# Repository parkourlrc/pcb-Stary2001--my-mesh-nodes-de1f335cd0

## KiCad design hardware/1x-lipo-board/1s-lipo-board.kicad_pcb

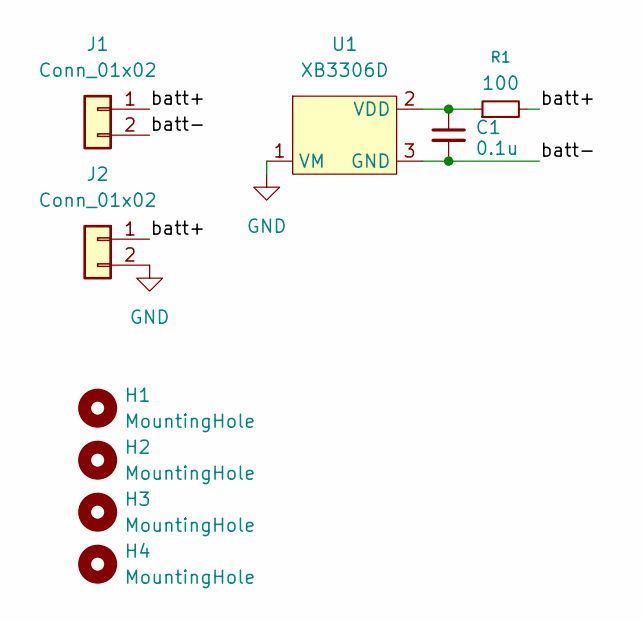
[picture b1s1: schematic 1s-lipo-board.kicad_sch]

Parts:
C1: 0.1u; C_0603_1608Metric
H1, H2, H3, H4: MountingHole; MountingHole_3.2mm_M3
J1: Conn_01x02; BatteryHolder_MPD_BK-18650-PC2
J2: Conn_01x02; JST_PH_S2B-PH-K_1x02_P2.00mm_Horizontal
R1: 100; R_0603_1608Metric
U1: XB3306D; SOT-23-3

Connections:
/batt+: J1.1, J2.1, R1.2
/batt-: C1.2, J1.2, U1.3 (GND)
GND: J2.2, U1.1 (VM)
unnamed: C1.1, R1.1, U1.2 (VDD)

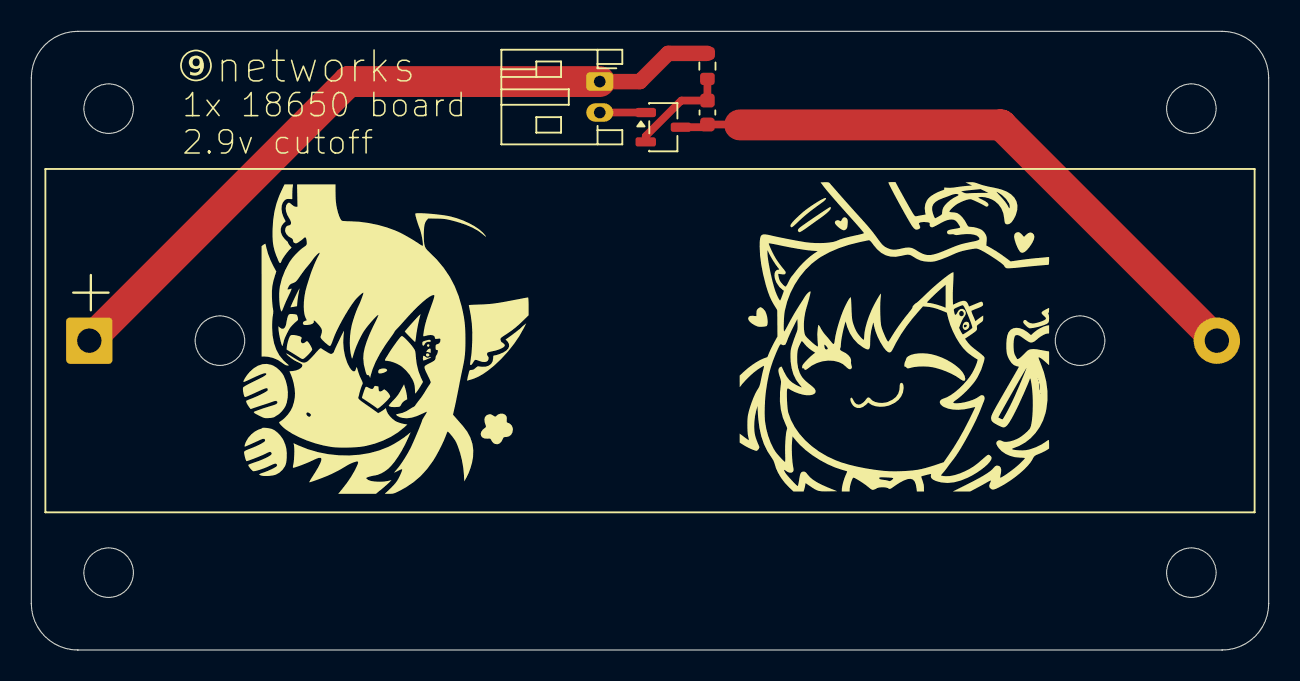
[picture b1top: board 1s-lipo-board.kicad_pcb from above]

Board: 2 copper layers, 80.0 x 40.0 mm, 9 parts (0 on the bottom side), 4 nets.

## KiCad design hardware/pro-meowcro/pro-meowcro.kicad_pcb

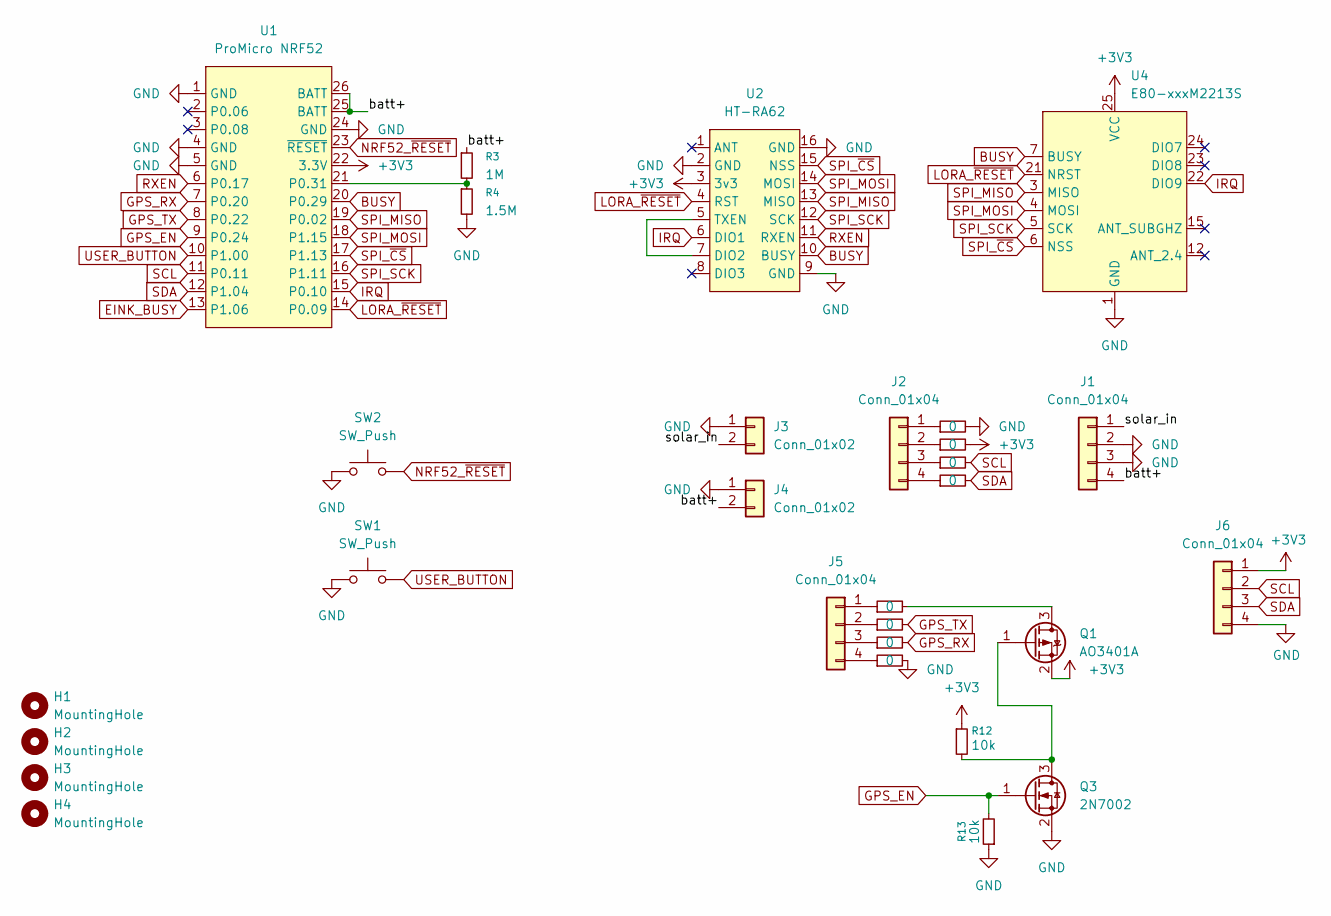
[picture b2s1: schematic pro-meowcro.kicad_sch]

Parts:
H1, H2, H3, H4: MountingHole; MountingHole_3.2mm_M3
J1, J2, J5: Conn_01x04; PinHeader_1x04_P2.54mm_Vertical
J3: Conn_01x02; JST_XH_B2B-XH-A_1x02_P2.50mm_Vertical
J4: Conn_01x02; JST_PH_B2B-PH-K_1x02_P2.00mm_Vertical
J6: Conn_01x04; JST_XH_B4B-XH-A_1x04_P2.50mm_Vertical
Q1: AO3401A; SOT-23
Q3: 2N7002; SOT-23
R1, R2, R5, R6, R7, R8, R9, R10: 0; R_0603_1608Metric
R3: 1M; R_0603_1608Metric
R4: 1.5M; R_0603_1608Metric
R12, R13: 10k; R_0603_1608Metric
SW1, SW2: SW_Push; SW_Tactile_SPST_NO_Straight_CK_PTS636Sx25SMTRLFS
U1: ProMicro NRF52; ProMicro_NRF52
U2: HT-RA62
U4: E80-xxxM2213S

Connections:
+3V3: J6.1, Q1.2 (S), R2.2, R12.1, U1.22 (3.3V), U2.3 (3v3), U4.25 (VCC)
/batt+: J1.4, J4.2, R3.1, U1.25 (BATT), U1.26 (BATT)
/solar_in: J1.1, J3.2
BUSY: U1.20 (P0.29), U2.10 (BUSY), U4.7 (BUSY)
EINK_BUSY: U1.13 (P1.06)
GND: J1.2, J1.3, J3.1, J4.1, J6.4, Q3.2 (S), R1.2, R4.2, R10.2, R13.1, SW1.1, SW2.1, U1.1 (GND), U1.4 (GND), U1.5 (GND), U1.24 (GND), U2.2 (GND), U2.9 (GND), U2.16 (GND), U4.1 (GND), U4.8 (GND), U4.11 (GND), U4.13 (GND), U4.14 (GND), U4.16 (GND), U4.19 (GND), U4.26 (GND)
GPS_EN: Q3.1 (G), R13.2, U1.9 (P0.24)
GPS_RX: R9.2, U1.7 (P0.20)
GPS_TX: R8.2, U1.8 (P0.22)
IRQ: U1.15 (P0.10), U2.6 (DIO1), U4.22 (DIO9)
LORA_~RESET: U1.14 (P0.09), U2.4 (RST), U4.21 (NRST)
NRF52_~RESET: SW2.2, U1.23 (~RESET)
unnamed: J2.1, R1.1
unnamed: J2.2, R2.1
unnamed: J2.3, R5.1
unnamed: J2.4, R6.1
unnamed: J5.1, R7.1
unnamed: J5.2, R8.1
unnamed: J5.3, R9.1
unnamed: J5.4, R10.1
unnamed: Q1.3 (D), R7.2
unnamed: Q1.1 (G), Q3.3 (D), R12.2
unnamed: R3.2, R4.1, U1.21 (P0.31)
unnamed: U2.5 (TXEN), U2.7 (DIO2)
RXEN: U1.6 (P0.17), U2.11 (RXEN)
SCL: J6.2, R5.2, U1.11 (P0.11)
SDA: J6.3, R6.2, U1.12 (P1.04)
SPI_MISO: U1.19 (P0.02), U2.13 (MISO), U4.3 (MISO)
SPI_MOSI: U1.18 (P1.15), U2.14 (MOSI), U4.4 (MOSI)
SPI_SCK: U1.16 (P1.11), U2.12 (SCK), U4.5 (SCK)
SPI_~CS: U1.17 (P1.13), U2.15 (NSS), U4.6 (NSS)
USER_BUTTON: SW1.2, U1.10 (P1.00)

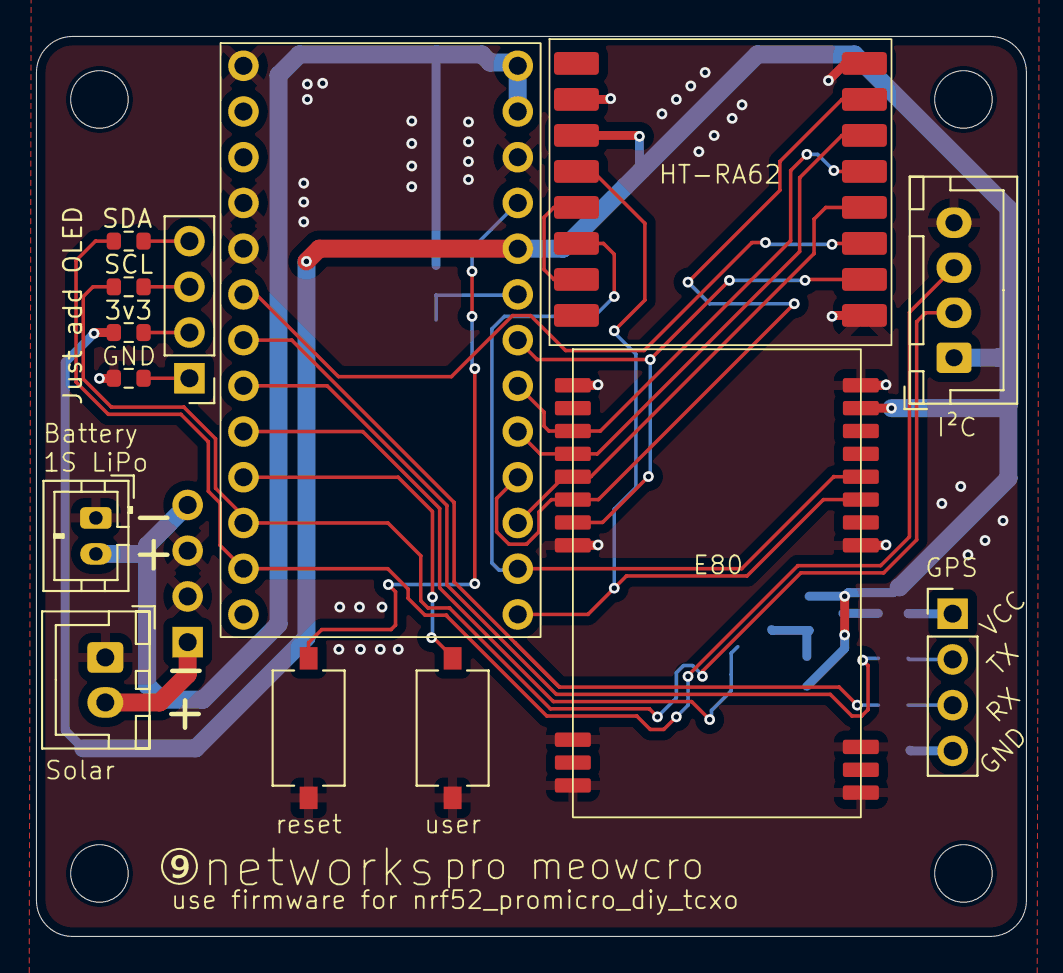
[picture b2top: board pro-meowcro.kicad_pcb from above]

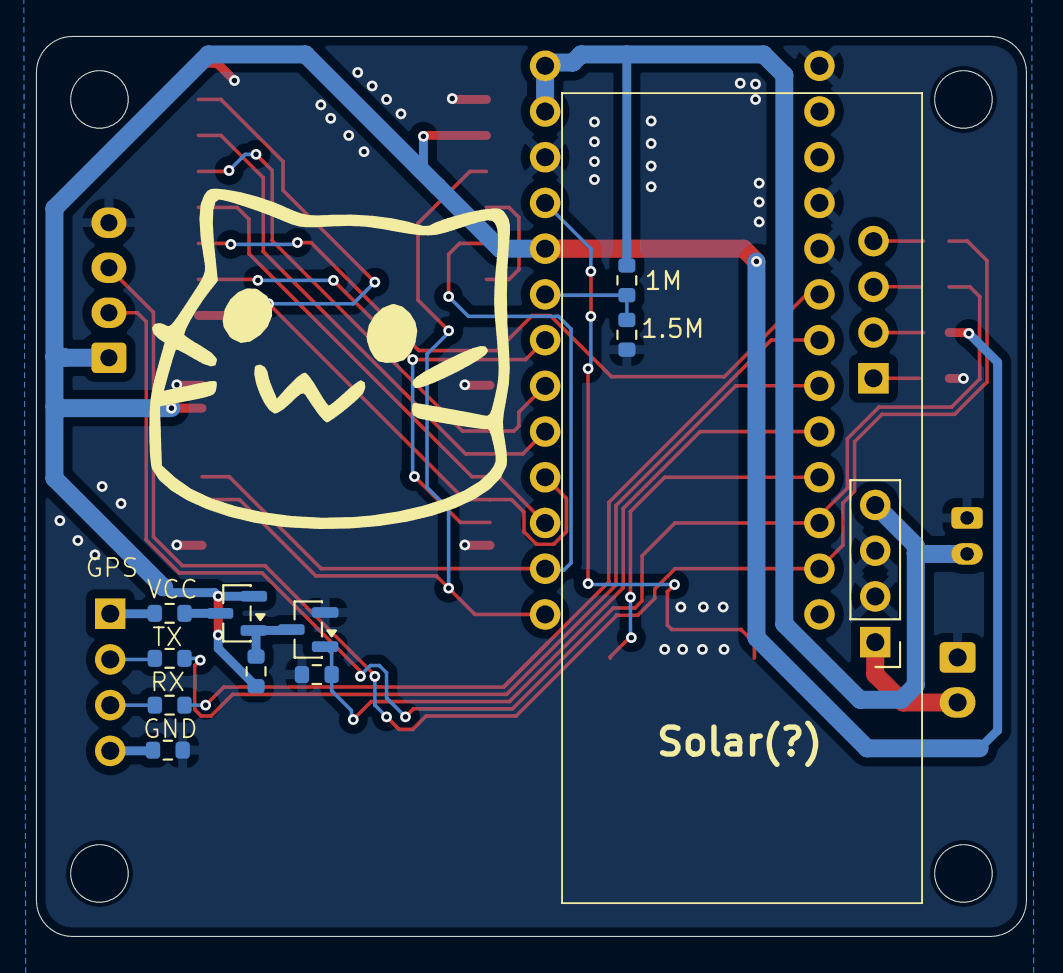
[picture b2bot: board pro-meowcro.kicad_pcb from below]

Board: 2 copper layers, 55.0 x 50.0 mm, 29 parts (11 on the bottom side), 31 nets.

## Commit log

2025-11-11 add pro meow
2025-11-11 add lipo->jst boards
